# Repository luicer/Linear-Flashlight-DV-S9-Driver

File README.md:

# Driver Lineal for diving flashlight  DV-S9
Design of a variable linear driver for the DV-S9 diving flashlight, the driver is capable of handling currents of up to 3 A the  input voltage range is between  3V and 4.2V, and has low standby current. The driver achieves an efficiency of between 90% and 70% at maximum current. This design is open source hardware.

Post where the design is esplained:
[https://luicer.github.io/led%20flashlight/Flashlight-Driver-Lineal-eng/](https://luicer.github.io/led%20flashlight/Flashlight-Driver-Lineal-eng/)

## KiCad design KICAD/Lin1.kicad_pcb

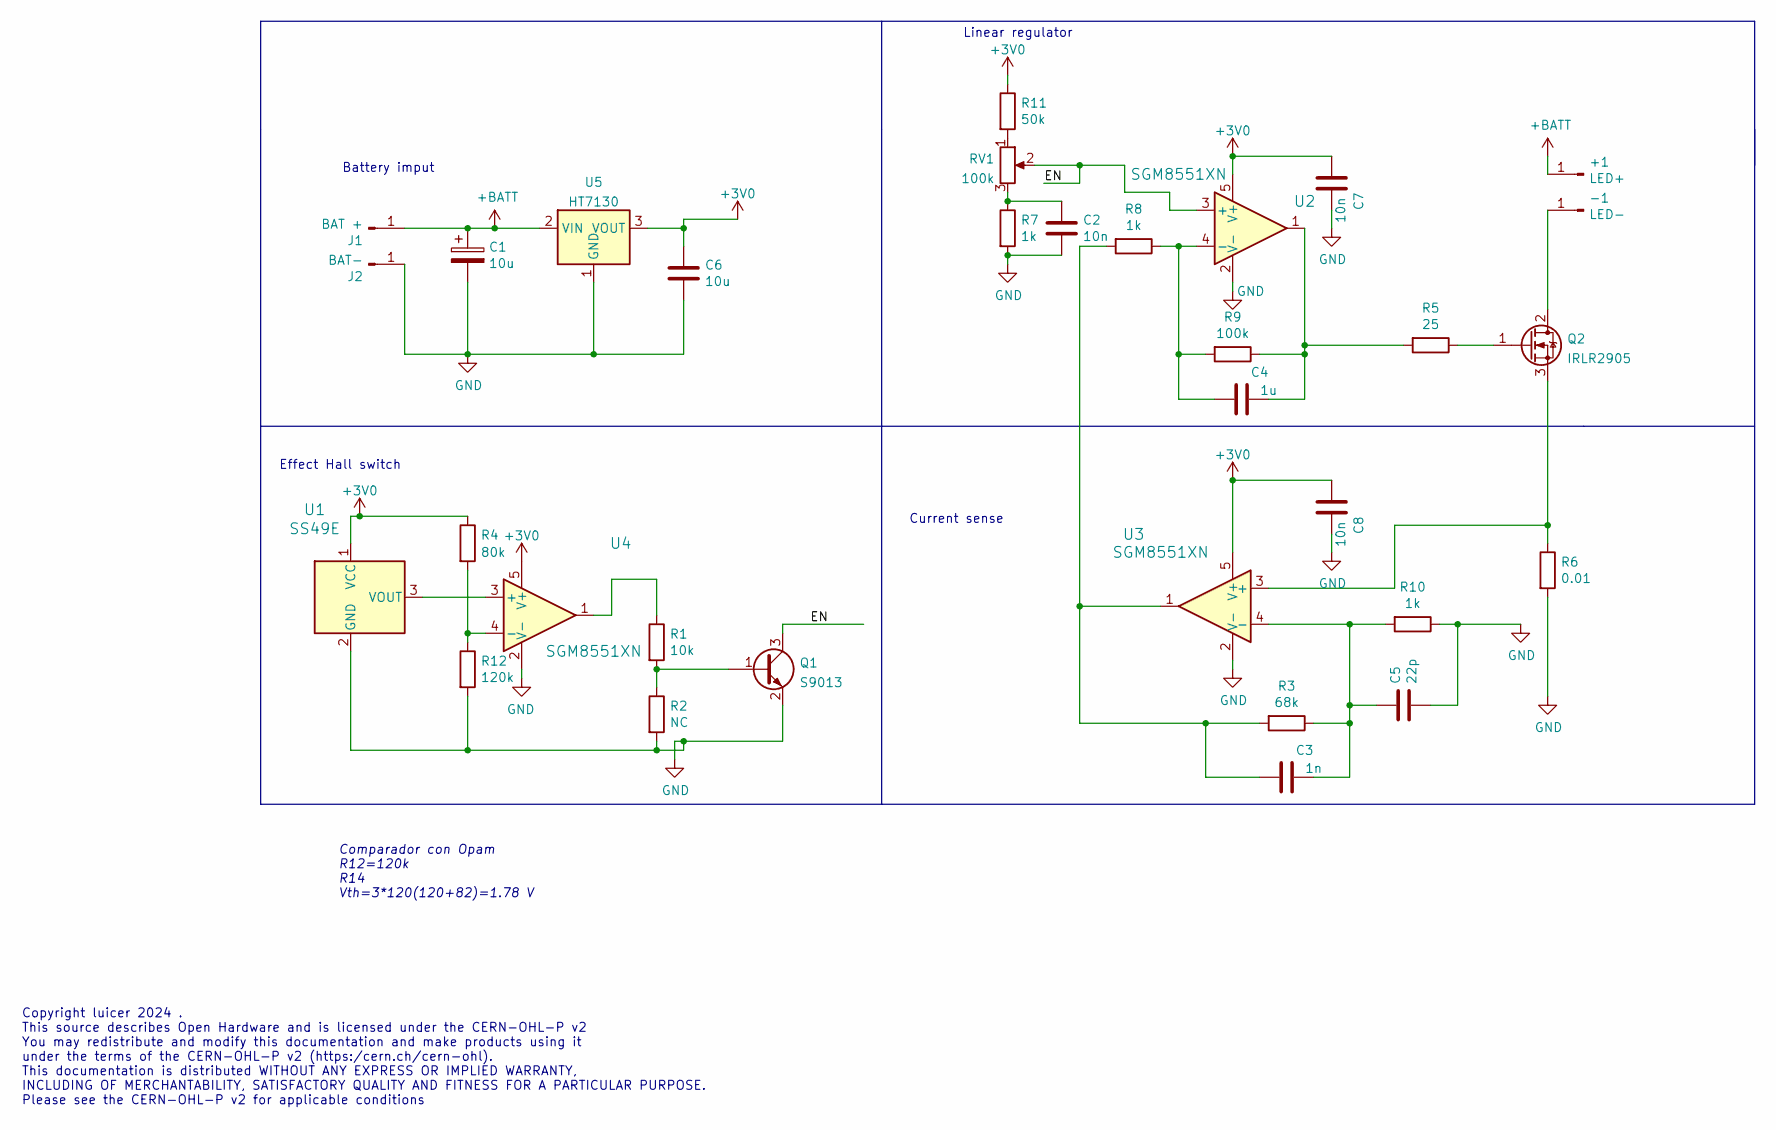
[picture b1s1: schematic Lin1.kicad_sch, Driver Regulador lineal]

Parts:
+1: LED+; Solder_Pad3_3
-1: LED-; Solder_Pad3_3
C1: 10u; CP_EIA-3216-18_Kemet-A_Pad1.58x1.35mm_HandSolder
C2: 10n; R_0805_2012Metric_Pad1.20x1.40mm_HandSolder
C3: 1n; C_0805_2012Metric_Pad1.15x1.40mm_HandSolder
C4: 1u; C_0805_2012Metric_Pad1.18x1.45mm_HandSolder
C5: 22p; C_0805_2012Metric_Pad1.15x1.40mm_HandSolder
C6: 10u; C_0805_2012Metric_Pad1.18x1.45mm_HandSolder
C7, C8: 10n; C_0805_2012Metric_Pad1.18x1.45mm_HandSolder
J1: BAT +; Lin_Pad+
J2: BAT-; Lin_Pad1-
Q1: S9013; SOT-23
Q2: IRLR2905; TO-252-3_TabPin2
R1: 10k; R_0805_2012Metric_Pad1.20x1.40mm_HandSolder
R2: NC; R_0805_2012Metric_Pad1.15x1.40mm_HandSolder
R3: 68k; R_0805_2012Metric_Pad1.15x1.40mm_HandSolder
R4: 80k; R_0805_2012Metric_Pad1.20x1.40mm_HandSolder
R5: 25; R_0805_2012Metric_Pad1.20x1.40mm_HandSolder
R6: 0.01; R_2512_6332Metric_Pad1.40x3.35mm_HandSolder
R7, R8, R10: 1k; R_0805_2012Metric_Pad1.20x1.40mm_HandSolder
R9: 100k; R_0805_2012Metric_Pad1.20x1.40mm_HandSolder
R11: 50k; R_0805_2012Metric_Pad1.20x1.40mm_HandSolder
R12: 120k; R_0805_2012Metric_Pad1.20x1.40mm_HandSolder
RV1: 100k; TC33X-2-103E
U1: SS49E
U2, U3, U4: SGM8551XN; SOT-23-5
U5: HT7130; SOT-89-3

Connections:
+3V0: C6.1, C7.2, C8.2, R4.1, R11.1, U1.1 (VCC), U2.5 (V+), U3.5 (V+), U4.5 (V+), U5.3 (VOUT)
+BATT: +1.1, C1.1, J1.1, U5.2 (VIN)
/EN: Q1.3 (C), RV1.2, U2.3 (+)
GND: C1.2, C2.2, C5.2, C6.2, C7.1, C8.1, J2.1, Q1.2 (E), R2.2, R6.2, R7.2, R10.1, R12.2, U1.2 (GND), U2.2 (V-), U3.2 (V-), U4.2 (V-), U5.1 (GND)
unnamed: -1.1, Q2.2 (D)
unnamed: C2.1, R7.1, RV1.3
unnamed: C3.1, C5.1, R3.1, R10.2, U3.4 (-)
unnamed: C3.2, R3.2, R8.2, U3.1
unnamed: C4.1, R5.2, R9.1, U2.1
unnamed: C4.2, R8.1, R9.2, U2.4 (-)
unnamed: Q1.1 (B), R1.2, R2.1
unnamed: Q2.1 (G), R5.1
unnamed: Q2.3 (S), R6.1, U3.3 (+)
unnamed: R1.1, U4.1
unnamed: R11.2, RV1.1
unnamed: R4.2, R12.1, U4.4 (-)
unnamed: U1.3 (VOUT), U4.3 (+)

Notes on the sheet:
Linear regulator
Copyright luicer 2024 . This source describes Open Hardware and is licensed under the CERN-OHL-P v2 You may redistribute and modify this documentation and make products using it under the terms of the CERN-OHL-P v2 (https:/cern.ch/cern-ohl). This documentation is distributed WITHOUT ANY EXPRESS OR 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
Battery imput
Effect Hall switch
Current sense
Comparador con Opam R12=120k R14 Vth=3*120(120+82)=1.78 V

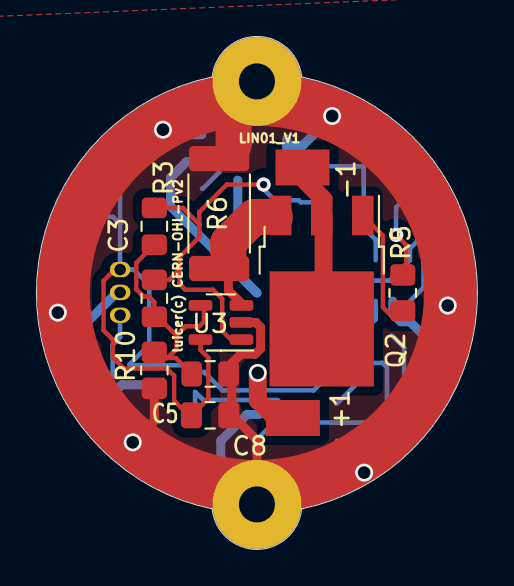
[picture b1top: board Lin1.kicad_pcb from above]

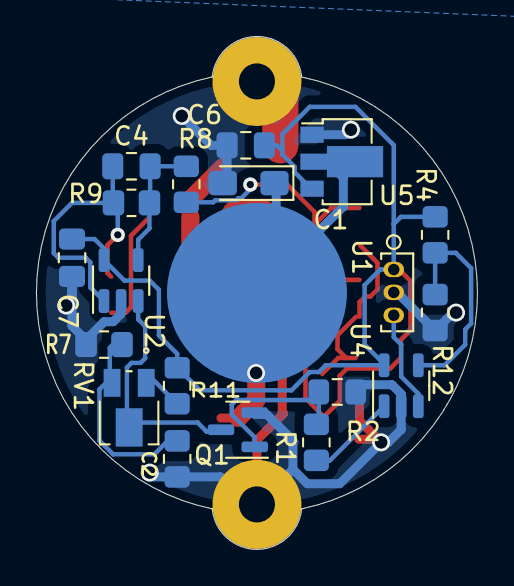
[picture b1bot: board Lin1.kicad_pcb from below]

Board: 2 copper layers, 24.5 x 28.5 mm, 32 parts (20 on the bottom side), 17 nets.

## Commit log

2024-02-21 Update LICENSE
2024-02-25 Add Design Files

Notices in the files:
KICAD/Lin1.kicad_pcb:
luicer(c) CERN-OHL-Pv2
parts and their libraries:
Copyright 2021 Accelerated Designs. All rights reserved.
